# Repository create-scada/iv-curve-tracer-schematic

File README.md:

Schematic for Impact Allies' Create-Scada [IV Curve Tracer workshop/labs](https://www.impactallies.com/iv-curve-tracer-lab). Drivers for the workshop can be found [here](https://github.com/create-scada/iv-curve-tracer-wifi). The schematic files are in KiCad format, 
and can be opened using the [KiCad](https://www.kicad.org/) open-source software.

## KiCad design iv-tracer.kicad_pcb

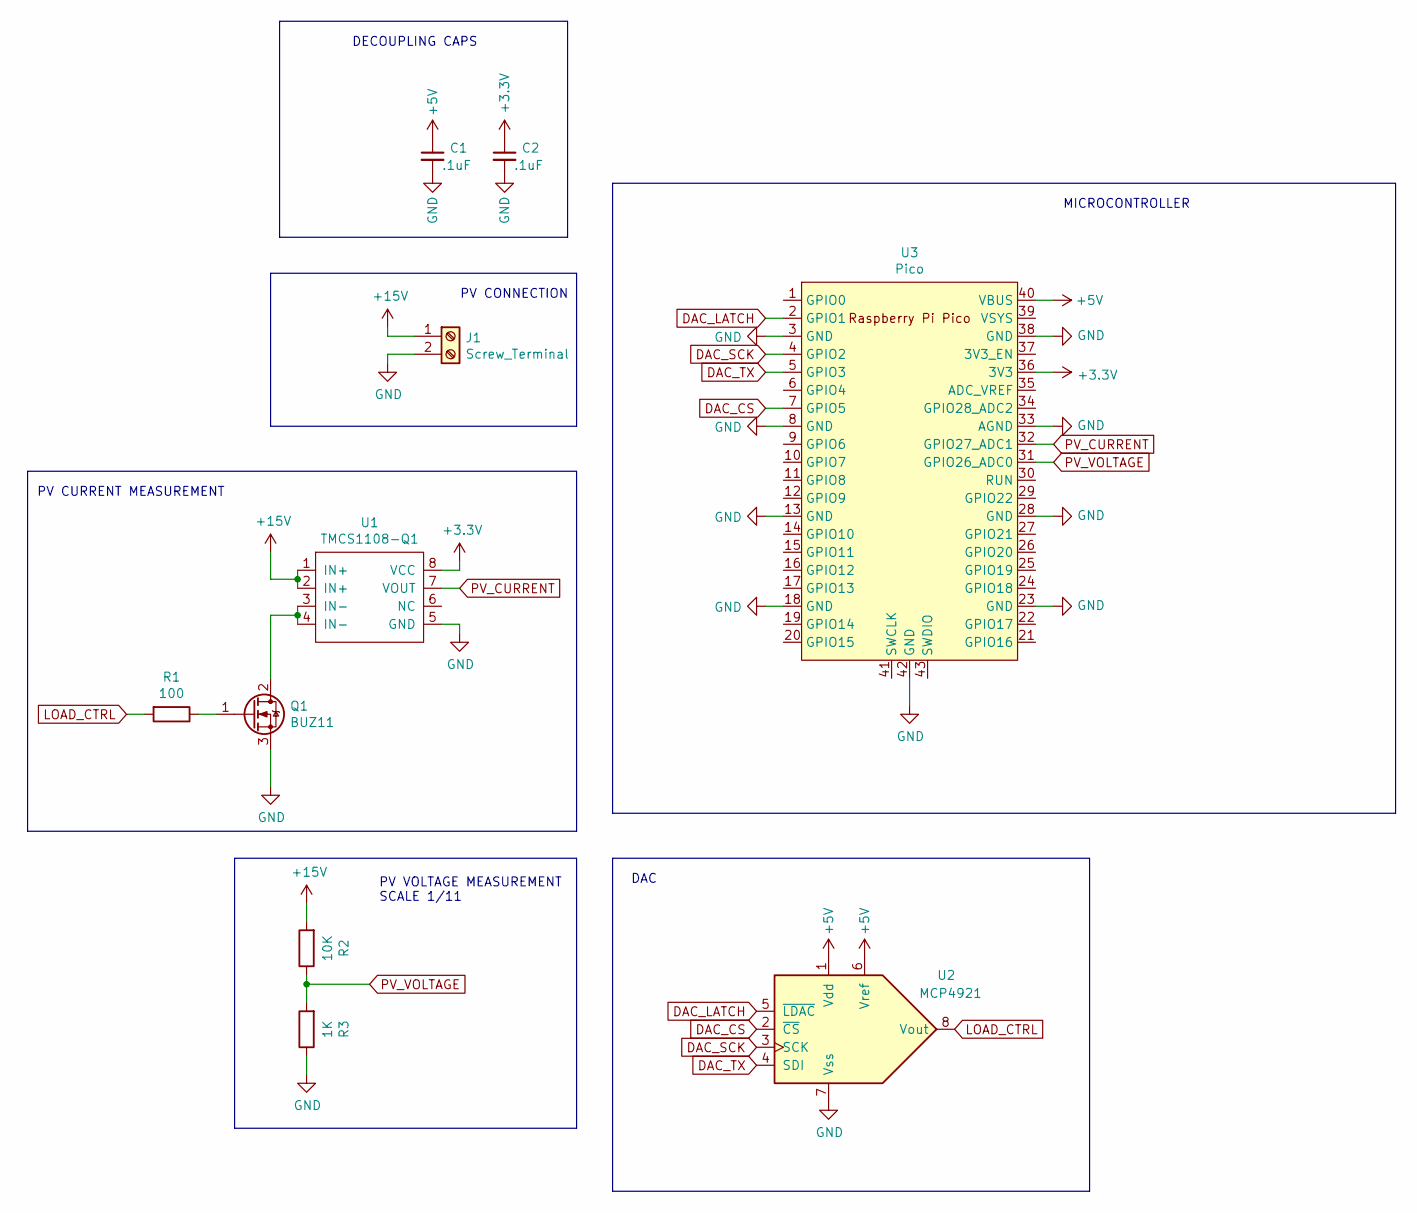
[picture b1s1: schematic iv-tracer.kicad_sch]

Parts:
C1, C2: .1uF; C_Disc_D5.0mm_W2.5mm_P5.00mm
J1: Screw_Terminal; PhoenixContact_GMSTBVA_2,5_2-G-7,62_1x02_P7.62mm_Vertical
Q1: BUZ11; TO-220-3_Vertical
R1: 100; R_Axial_DIN0204_L3.6mm_D1.6mm_P5.08mm_Horizontal
R2: 10K; R_Axial_DIN0204_L3.6mm_D1.6mm_P5.08mm_Horizontal
R3: 1K; R_Axial_DIN0204_L3.6mm_D1.6mm_P5.08mm_Horizontal
U1: TMCS1108-Q1; SOIC-8_3.9x4.9mm_P1.27mm
U2: MCP4921; SOIC-8_3.9x4.9mm_P1.27mm
U3: Pico; RPi_Pico_SMD_TH

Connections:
+3V3: C2.1, U1.8 (VCC), U3.36 (3V3)
+5V: C1.1, U2.1 (Vdd), U2.6 (Vref), U3.40 (VBUS)
+15V: J1.1, R2.2, U1.1 (IN+), U1.2 (IN+)
DAC_CS: U2.2 (~CS), U3.7 (GPIO5)
DAC_LATCH: U2.5 (~LDAC), U3.2 (GPIO1)
DAC_SCK: U2.3 (SCK), U3.4 (GPIO2)
DAC_TX: U2.4 (SDI), U3.5 (GPIO3)
GND: C1.2, C2.2, J1.2, Q1.3 (S), R3.1, U1.5 (GND), U2.7 (Vss), U3.3 (GND), U3.8 (GND), U3.13 (GND), U3.18 (GND), U3.23 (GND), U3.28 (GND), U3.33 (AGND), U3.38 (GND), U3.42 (GND)
GPIO6: U3.9 (GPIO6)
GPIO7: U3.10 (GPIO7)
GPIO8: U3.11 (GPIO8)
GPIO9: U3.12 (GPIO9)
GPIO10: U3.14 (GPIO10)
GPIO11: U3.15 (GPIO11)
GPIO12: U3.16 (GPIO12)
GPIO13: U3.17 (GPIO13)
LOAD_CTRL: R1.2, U2.8 (Vout)
unnamed: Q1.1 (G), R1.1
unnamed: Q1.2 (D), U1.3 (IN-), U1.4 (IN-)
PV_CURRENT: U1.7 (VOUT), U3.32 (GPIO27_ADC1)
PV_VOLTAGE: R2.1, R3.2, U3.31 (GPIO26_ADC0)

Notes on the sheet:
PV CURRENT MEASUREMENT
DAC
PV VOLTAGE MEASUREMENT SCALE 1/11
PV CONNECTION
MICROCONTROLLER
DECOUPLING CAPS

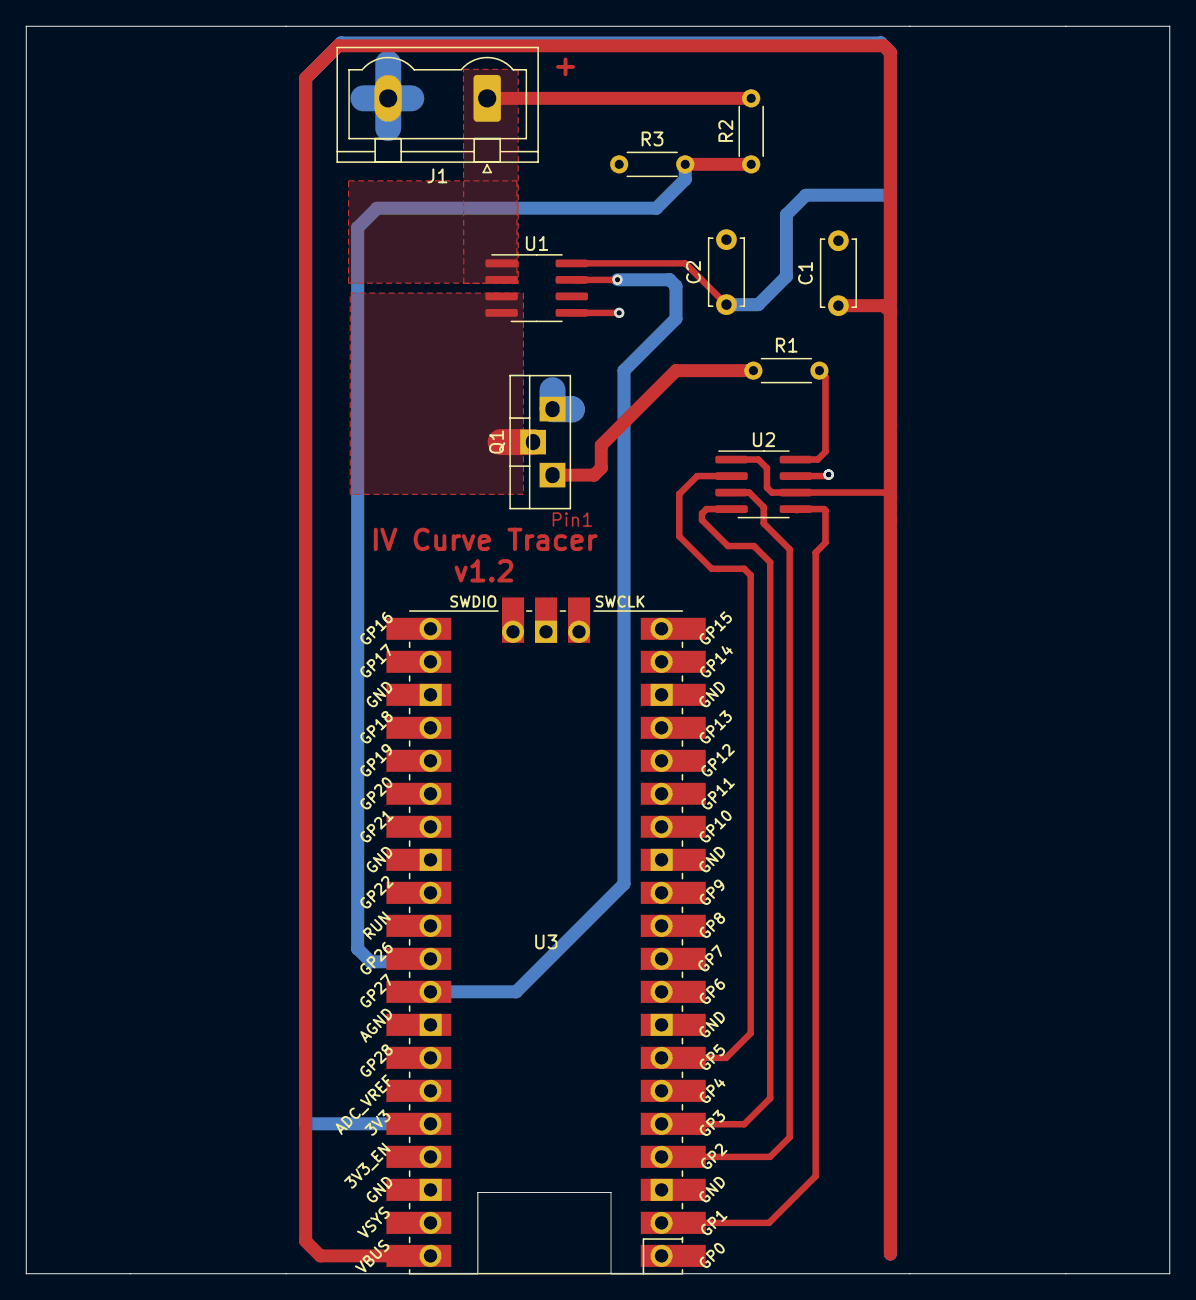
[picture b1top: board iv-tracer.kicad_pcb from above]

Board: 2 copper layers, 88.0 x 96.0 mm, 10 parts (0 on the bottom side), 13 nets.
